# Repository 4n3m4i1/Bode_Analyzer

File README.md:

# Bode Bandits Analysis Tool
The Bode Bandits Analysis Tool provides frequency response characteristics of a multitude of filters.
A Python GUI allows interface with the tool, providing configuration and visual representations of the measured transfer function.  
  
## Hardware
Board and assembly files are provided in the repository, optimized for JLC's PCBA service.  
  
## Methods
The Least Mean Squared (LMS) adaptive filter methodology is implemented in a semi-real time fashion, allowing rapid characterization cycles to be made.  
All algorithms (LMS, FFT, Downsampling) are fully parametric, and largely user selectable on the fly. Automatic self-calibration corrects for  
component tolerance variations, VDDA magnitude, and the frontend anti-aliasing filter transfer function. DC calibration routines are run at  
startup, all transfer function calibration metrics are gathered at startup as well as upon change of any parametric setting.  

## Real Time Adjustment Parameters
- Range of frequency analysis (set ranges)
- Datapoint resolution (2^n)
- Acceptable LMS convergence error tolerances
  
## Required User Software 
- Python 3.9+
- That's it :)
  
## Repo Layout
- App: Contains the PC side of the project. Including the Python source and helper tools.
- HDL: Placeholder for potential HDL in the event a switch to a more PL based approach occurs.
- src: All C source for both the current main build as well as helper C files and feature tests.
- Documentation: All standard documentation as well as theory behind every working component, with test programs and scrips included.

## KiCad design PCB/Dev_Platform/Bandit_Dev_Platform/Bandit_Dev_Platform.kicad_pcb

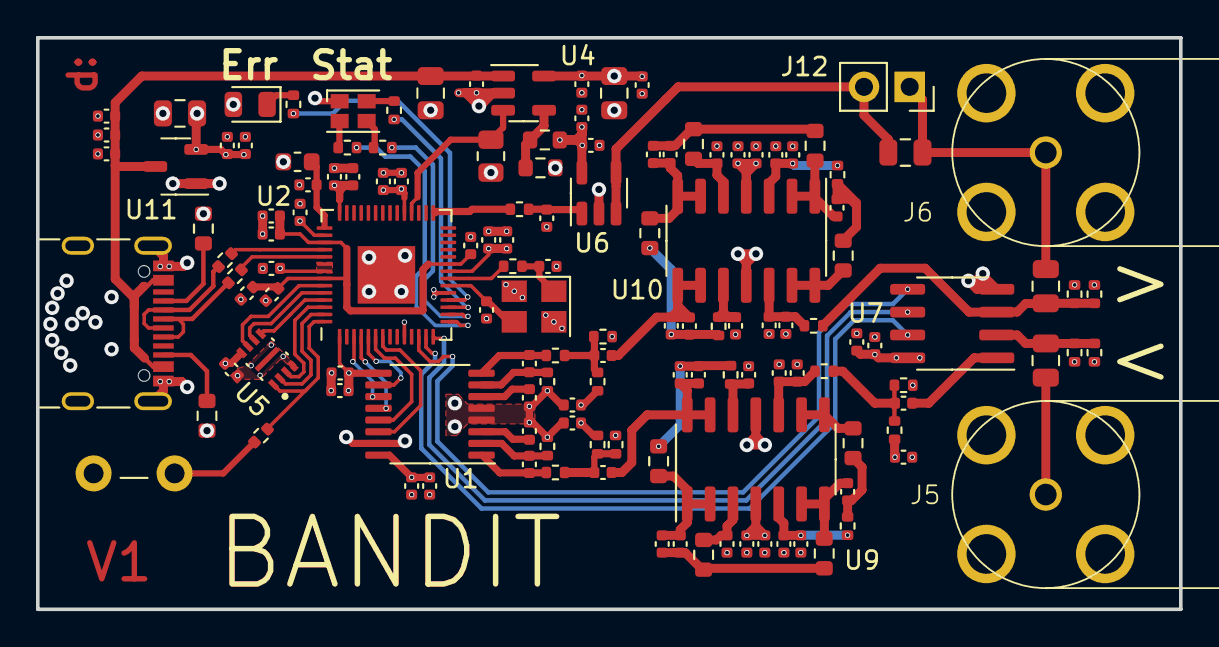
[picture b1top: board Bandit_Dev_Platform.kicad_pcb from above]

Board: 4 copper layers, 63.5 x 31.8 mm, 136 parts (0 on the bottom side), 79 nets.

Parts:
C1, C3, C3#2, C6, C8, C12, C13, C15, C26, C28, C31, C33, C36, C48, C57, C61, C62, C64, C65, C67, C74: 100n; C_0402_1005Metric
C2, C17, C18, C21, C22, C68: 10u; C_0402_1005Metric
C4, C9, C14, C27, C29, C30: 1u; C_0402_1005Metric
C5, C35, C49, C58: 10n; C_0402_1005Metric
C7, C10, C16, C19, C20, C38, C41, C46, C50, C55: 33p C0G; C_0402_1005Metric
C11, C34, C37, C63, C66, C70: 2u2; C_0402_1005Metric
C23, C24: 16n C0G; C_0402_1005Metric
C25, C69, C71, C72, C73, C75: 10u 0805; C_0805_2012Metric
C32: 10n C0G; C_0402_1005Metric
C39, C40, C45, C47, C54, C56: 100p C0G; C_0402_1005Metric
C42, C51: 15p C0G; C_0402_1005Metric
C43, C52: 220p C0G; C_0402_1005Metric
C44, C53, C59, C60: 47p C0G; C_0402_1005Metric
D1: LED; LED_0805_2012Metric
D2: LED_ABGR; LED_Cree-PLCC4_2x2mm_CW
FB1: FerriteBead_Small; L_0603_1608Metric
J5, J6: BNC; DOSIN-801-0050
J12: Conn_01x02_Pin; PinSocket_1x02_P2.54mm_Vertical
P1: USB_C_Plug_USB2.0; USB_C_Receptacle_GCT_USB4105-xx-A_16P_TopMnt_Horizontal
R1, R2, R3, R6: 330R; R_0402_1005Metric
R4, R5: 27R; R_0402_1005Metric
R7: 10k; R_0805_2012Metric
R8: 150k; R_0603_1608Metric
R9: 50k; R_0603_1608Metric
R10, R11: 56k; R_0603_1608Metric
R12, R14: 1k; R_0402_1005Metric
R13, R15, R25, R26: 51k; R_0402_1005Metric
R16, R17, R18, R19, R20, R42: 10k; R_0402_1005Metric
R21, R22, R23, R24: 20R; R_0402_1005Metric
R27: 8.06; R_0402_1005Metric
R28, R32, R35, R39: 15k; R_0402_1005Metric
R29, R36: 8k2; R_0603_1608Metric
R30, R37: 15k; R_0603_1608Metric
R31, R38: 5k6; R_0603_1608Metric
R33, R40: 6k2; R_0603_1608Metric
R34, R41: 12k; R_0402_1005Metric
SW1: SW_SPST; SW_PUSH_6mm
U1: AD7253; TSSOP-16_4.4x5mm_P0.65mm
U2: RP2040; QFN-56-1EP_7x7mm_P0.4mm_EP3.2x3.2mm
U4: NCP164ASNADJT1G; SOT-23-5
U5: W25Q16JVUXIQ_TR; IC_W25Q16JVUXIQ_TR
U6: MCP6486UT-E/OT; SOT-23-5
U7: MCP6S92-E/SN; SOIC-8_3.9x4.9mm_P1.27mm
U9, U10: OPA1664; SOIC-14_3.9x8.7mm_P1.27mm
U11: XC6206PxxxMR; SOT-23-3
Y1: 12.000 MHz, C9002; Crystal_SMD_3225-4Pin_3.2x2.5mm

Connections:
+1V1: C33.1, C34.1, C62.1, C63.1, C64.1, U2.23 (DVDD), U2.45 (VREG_VOUT), U2.50 (DVDD)
+3V3: C1.1, C28.1, C29.1, C35.1, C36.1, C37.1, C61.1, C65.1, C66.1, C67.1, C68.1, C69.1, C70.1, C74.1, D1.2 (A), D2.1 (A), FB1.2, U1.9 (DVDD), U2.1 (IOVDD), U2.10 (IOVDD), U2.22 (IOVDD), U2.33 (IOVDD), U2.42 (IOVDD), U2.44 (VREG_IN), U2.48 (USB_VDD), U2.49 (IOVDD), U5.8 (VCC), U11.2 (VO)
/ADC_CSN: U1.11 (~CS), U2.3 (GPIO1)
/ADC_SCK: U1.12 (SCLK), U2.4 (GPIO2)
/ADC_SDI: U1.10 (SDI), U2.5 (GPIO3)
/ADC_SDO_A: U1.13 (SDO_A), U2.6 (GPIO4)
/ADC_SDO_B: U1.14 (SDO_B), U2.7 (GPIO5)
/CLK_12M: C10.1, U2.20 (XIN), Y1.3
/FLASH_IO0: U2.53 (QSPI_SD0), U5.5 (DI(IO0))
/FLASH_IO1: U2.55 (QSPI_SD1), U5.2 (DO(IO1))
/FLASH_IO2: U2.54 (QSPI_SD2), U5.3 (IO2)
/FLASH_IO3: U2.51 (QSPI_SD3), U5.7 (IO3)
/FLASH_SCK: U2.52 (QSPI_SCLK), U5.6 (CLK)
/LED_B: R1.2, U2.17 (GPIO14)
/LED_G: R2.2, U2.16 (GPIO13)
/LED_R: R3.2, U2.15 (GPIO12)
/PDM_WGN: R27.2, U2.29 (GPIO18)
/PGA_SCK: U2.13 (GPIO10), U7.7 (SCK)
/PGA_SI: U2.14 (GPIO11), U7.6 (SI)
/SE_SIG_A: C18.2, C39.1, C52.1, U10.8, U10.9 (-)
/SE_SIG_B: C17.2, C40.1, C43.1, U9.13 (-), U9.14
/SIG_IN: C2.1, R16.2, R17.1, R34.1
/USB_CC: P1.A5 (CC), R10.1
/USB_D+: R5.2, U2.47 (USB_DP)
/USB_D-: R4.2, U2.46 (USB_DM)
/USB_VCONN: P1.B5 (VCONN), R11.1
/USER_LED: R6.2, U2.18 (GPIO15)
/VDDA_EN: R7.2, U2.32 (GPIO21), U4.3 (EN)
/WGN_OUT: C73.2, J12.2, U6.3 (VIN-), U6.4 (VOUT)
/WGN_OUT_PORT: C72.1, C73.1, J6.1 (In), J12.1
/WGN_PGA_IN: C72.2, R13.2, R15.1, R41.1, U7.3 (CH1)
/XOUT: C7.2, R14.2, Y1.1
/~FLASH_CSN: R12.1, U2.56 (QSPI_SS), U5.1 (~CS)
/~PGA_CS: U2.12 (GPIO9), U7.5 (~CS)
GND: C1.2, C3.2, C3#2.2, C4.2, C5.2, C6.2, C7.1, C8.2, C9.2, C10.2, C11.2, C12.2, C13.2, C14.2, C15.2, C16.1, C19.1, C20.1, C21.2, C22.2, C26.2, C27.2, C28.2, C29.2, C30.2, C31.2, C32.2, C33.2, C34.2, C35.2, C36.2, C37.2, C38.1, C41.1, C42.1, C44.1, C46.1, C48.2, C49.2, C50.1, C51.1, C53.1, C55.1, C57.2, C58.2, C61.2, C62.2, C63.2, C64.2, C65.2, C66.2, C67.2, C68.2, C69.2, C70.2, C71.2, C74.2, C75.2, J5.2 (Ext), J6.2 (Ext), P1.A1 (GND), P1.A12 (GND), P1.B1 (GND), P1.B12 (GND), P1.S1 (SHIELD), R7.1, R9.1, R10.2, R11.2, R15.2, R17.2, R19.2, R21.1, R24.1, R26.2, R42.2, SW1.2 (B), U1.4 (REFGND_A), U1.5 (REFGND_B), U1.15 (GND), U2.19 (TESTEN), U2.57 (GND), U4.2 (GND), U5.4 (GND), U6.2 (VSS), U7.4 (VSS), U9.11 (V-), U10.11 (V-), U11.1 (GND), Y1.2, Y1.4
unnamed: C17.1, R18.2, R19.1, R23.1
unnamed: C18.1, R20.2, R22.1, R42.1
unnamed: C39.2, C52.2, R35.1, R36.2
unnamed: C40.2, C43.2, R28.1, R29.2
unnamed: C45.2, C60.2, R30.1, R31.2
unnamed: C47.2, R32.1, R33.2
unnamed: C54.2, C59.2, R37.1, R38.2
unnamed: C56.2, R39.1, R40.2
unnamed: D1.1 (K), R6.1
unnamed: D2.2 (BK), R1.1
unnamed: D2.3 (GK), R2.1
unnamed: D2.4 (RK), R3.1
unnamed: C25.1, J5.1 (In)
unnamed: P1.A6 (D+), R5.1
unnamed: P1.A7 (D-), R4.1
unnamed: R12.2, SW1.1 (A)
unnamed: C24.2, R24.2, U1.2 (AINM_A)
unnamed: C23.2, R21.2, U1.7 (AINM_B)
unnamed: C24.1, R23.2, U1.1 (AINP_A)
unnamed: C23.1, R22.2, U1.8 (AINP_B)
unnamed: C22.1, U1.3 (REFIO_A)
unnamed: C21.1, U1.6 (REFIO_B)
unnamed: C11.1, FB1.1, U2.43 (ADC_AVDD)
unnamed: R14.1, U2.21 (XOUT)
unnamed: R8.1, R9.2, U4.4 (PG/ADJ)
unnamed: C32.1, R27.1, U6.1 (VIN+)
unnamed: C25.2, R25.2, R26.1, U7.2 (CH0)
unnamed: C2.2, U7.1 (VOUT)
unnamed: C44.2, R30.2, U9.3 (+)
unnamed: C45.1, C60.1, R29.1, U9.1, U9.2 (-)
unnamed: C16.2, C46.2, R32.2, U9.5 (+)
unnamed: C47.1, R31.1, U9.6 (-), U9.7
unnamed: C19.2, C50.2, R34.2, U9.10 (+)
unnamed: R33.1, U9.8, U9.9 (-)
unnamed: C42.2, R28.2, U9.12 (+)
unnamed: C38.2, C55.2, R39.2, U10.3 (+)
unnamed: C56.1, R38.1, U10.1, U10.2 (-)
unnamed: C53.2, R37.2, U10.5 (+)
unnamed: C54.1, C59.1, R36.1, U10.6 (-), U10.7
unnamed: C51.2, R35.2, U10.10 (+)
unnamed: C20.2, C41.2, R41.2, U10.12 (+)
unnamed: R40.1, U10.13 (-), U10.14
VBUS: C3.1, C4.1, C5.1, C6.1, C75.1, P1.A4 (VBUS), P1.A9 (VBUS), P1.B4 (VBUS), P1.B9 (VBUS), U4.1 (VIN), U11.3 (VI)
VDDA: C3#2.1, C8.1, C9.1, C12.1, C13.1, C14.1, C15.1, C26.1, C27.1, C30.1, C31.1, C48.1, C49.1, C57.1, C58.1, C71.1, R8.2, R13.1, R16.1, R18.1, R20.1, R25.1, U1.16 (AVDD), U4.5 (VOUT), U6.5 (VDD), U7.8 (VDD), U9.4 (V+), U10.4 (V+)

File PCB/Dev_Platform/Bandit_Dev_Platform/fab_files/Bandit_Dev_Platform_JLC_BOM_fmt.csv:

Designator,Qty,Value,Footprint,LCSC Part Number,
"C1, C3, C6, C8, C12, C13, C15, C26, C28, C31, C33, C36, C48, C57, C61, C62, C64, C65, C67, C74",20,100n,Capacitor_SMD:C_0402_1005Metric,C307331,
"C2, C17, C18, C21, C22, C68",6,10u,Capacitor_SMD:C_0402_1005Metric,C15525,
"C4, C9, C14, C27, C29, C30",6,1u,Capacitor_SMD:C_0402_1005Metric,C52923,
"C5, C35, C49, C58",4,10n,Capacitor_SMD:C_0402_1005Metric,C15195,
"C7, C10, C19, C20, C41, C50",6,33p C0G,Capacitor_SMD:C_0402_1005Metric,C1562,
"C11, C34, C37, C63, C66",6,2u2,Capacitor_SMD:C_0402_1005Metric,C12530,
"C16, C38, C46, C55",4,33p,C0G,Capacitor_SMD:C_0402_1005Metric,C1562
"C23, C24",2,16n C0G,Capacitor_SMD:C_0402_1005Metric,C1549,
"C25, C69, C70, C71, C72, C73",5,10u 0805,Capacitor_SMD:C_0805_2012Metric,C440198,
C32,1,10n C0G,Capacitor_SMD:C_0402_1005Metric,C15195,
"C39, C40, C45, C47, C54, C56",6,100p,C0G,Capacitor_SMD:C_0402_1005Metric,C1546
"C42, C51",2,15p   C0G,Capacitor_SMD:C_0402_1005Metric,C1548,
C43,1,220p,C0G,Capacitor_SMD:C_0402_1005Metric,C1530
"C44, C53, C59, C60",4,47p,C0G,Capacitor_SMD:C_0402_1005Metric,C1567
C52,1,220p C0G,Capacitor_SMD:C_0402_1005Metric,C1530,
D1,1,LED,LED_SMD:LED_0805_2012Metric,C2297,
D2,1,LED_ABGR,LED_SMD:LED_Cree-PLCC4_2x2mm_CW,C2874119,
FB1,1,FerriteBead_Small,Inductor_SMD:L_0603_1608Metric,C1002,
"J5, J6",2,BNC,BANDIT_PCB_Lib:DOSIN-801-0050,C521210,
P1,1,USB_C_Plug_USB2.0,Connector_USB:USB_C_Receptacle_GCT_USB4105-xx-A_16P_TopMnt_Horizontal,C963413,
"R1, R2, R3, R6",4,330R,Resistor_SMD:R_0402_1005Metric,C25104,
"R4, R5",2,27R,Resistor_SMD:R_0402_1005Metric,C25092,
R7,1,100k,Resistor_SMD:R_0805_2012Metric,C149504,
R8,1,150k,Resistor_SMD:R_0603_1608Metric,C22807,
R9,1,50k,Resistor_SMD:R_0603_1608Metric,C23184,
"R10, R11",2,56k,Resistor_SMD:R_0603_1608Metric,C23206,
"R12, R14",2,1k,Resistor_SMD:R_0402_1005Metric,C11702,
"R13, R15, R25, R26",4,51k,Resistor_SMD:R_0402_1005Metric,C25794,
"R16, R17, R18, R19, R20, R42",6,10k,Resistor_SMD:R_0402_1005Metric,C25744,
"R21, R22, R23, R24",4,20R,Resistor_SMD:R_0402_1005Metric,C25092,
R27,1,8.06,Resistor_SMD:R_0402_1005Metric,C25077,
"R28, R32, R35, R39",4,15k,Resistor_SMD:R_0402_1005Metric,C25867,
"R29, R36",2,8k2,Resistor_SMD:R_0603_1608Metric,C25981,
"R30, R37",2,15k,Resistor_SMD:R_0603_1608Metric,C22809,
"R31, R38",2,5k6,Resistor_SMD:R_0603_1608Metric,C23189,
"R33, R40",2,6k2,Resistor_SMD:R_0603_1608Metric,C4260,
"R34, R41",2,12k,Resistor_SMD:R_0402_1005Metric,C25752,
U2,1,RP2040,Package_DFN_QFN:QFN-56-1EP_7x7mm_P0.4mm_EP3.2x3.2mm,C2040,
U5,1,W25Q16JVUXIQ_TR,ICDB_Curly:IC_W25Q16JVUXIQ_TR,C2843335,
U11,1,XC6206PxxxMR,Package_TO_SOT_SMD:SOT-23-3,C5446,
Y1,1,"	12.000 MHz, C9002 ",Crystal:Crystal_SMD_3225-4Pin_3.2x2.5mm,C9002,

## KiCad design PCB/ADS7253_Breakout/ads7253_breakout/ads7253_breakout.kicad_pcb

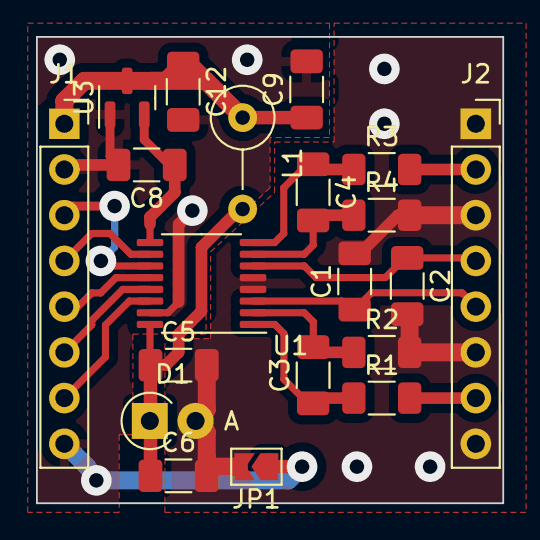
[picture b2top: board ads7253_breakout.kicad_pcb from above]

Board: 2 copper layers, 25.9 x 25.9 mm, 20 parts (0 on the bottom side), 18 nets.

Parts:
C1, C2: 10u; C_1206_3216Metric_Pad1.33x1.80mm_HandSolder
C3, C4: 16p; C_1206_3216Metric_Pad1.33x1.80mm_HandSolder
C5, C9, C12: 1u; C_1206_3216Metric_Pad1.33x1.80mm_HandSolder
C6, C8: 100n; C_1206_3216Metric_Pad1.33x1.80mm_HandSolder
D1: D_Zener; D_T-1_P2.54mm_Vertical_AnodeUp
J1, J2: Conn_01x08_Pin; PinSocket_1x08_P2.54mm_Vertical
JP1: Jumper_2_Bridged; SolderJumper-2_P1.3mm_Open_TrianglePad1.0x1.5mm
L1: L; L_Axial_L7.0mm_D3.3mm_P5.08mm_Vertical_Fastron_MICC
R1, R2, R3, R4: 20R; R_1206_3216Metric_Pad1.30x1.75mm_HandSolder
U1: AD7253; TSSOP-16_4.4x5mm_P0.65mm
U3: MCP1700x-330xxTT; SOT-23

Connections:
+3V3: C8.1, U1.9 (DVDD), U3.2 (VO)
+5C: C9.1, C12.1, J1.1, L1.1, U3.3 (VI)
/AINP_A_1: J2.7, R1.2
/AINP_B_8: J2.2, R3.2
/REFDAC_A: C1.1, J2.5, U1.3 (REFIO_A)
/REFDAC_B: C2.1, J2.4, U1.6 (REFIO_B)
/SPI_CSN: J1.3, U1.11 (~CS)
/SPI_SCLK: J1.5, U1.12 (SCLK)
/SPI_SDI: J1.4, U1.10 (SDI)
/SPI_SDOA: J1.6, U1.13 (SDO_A)
/SPI_SDOB: J1.7, U1.14 (SDO_B)
GND: C8.2, C9.2, C12.2, J1.2, J1.8, JP1.1 (A), U1.15 (GND), U3.1 (GND)
GNDA: C1.2, C2.2, C5.2, C6.2, D1.2 (A), J2.1, J2.3, J2.6, J2.8, JP1.2 (B), R2.2, R4.2, U1.4 (REFGND_A), U1.5 (REFGND_B)
unnamed: C3.2, R2.1, U1.2 (AINM_A)
unnamed: C4.2, R4.1, U1.7 (AINM_B)
unnamed: C3.1, R1.1, U1.1 (AINP_A)
unnamed: C4.1, R3.1, U1.8 (AINP_B)
VDDA: C5.1, C6.1, D1.1 (K), L1.2, U1.16 (AVDD)

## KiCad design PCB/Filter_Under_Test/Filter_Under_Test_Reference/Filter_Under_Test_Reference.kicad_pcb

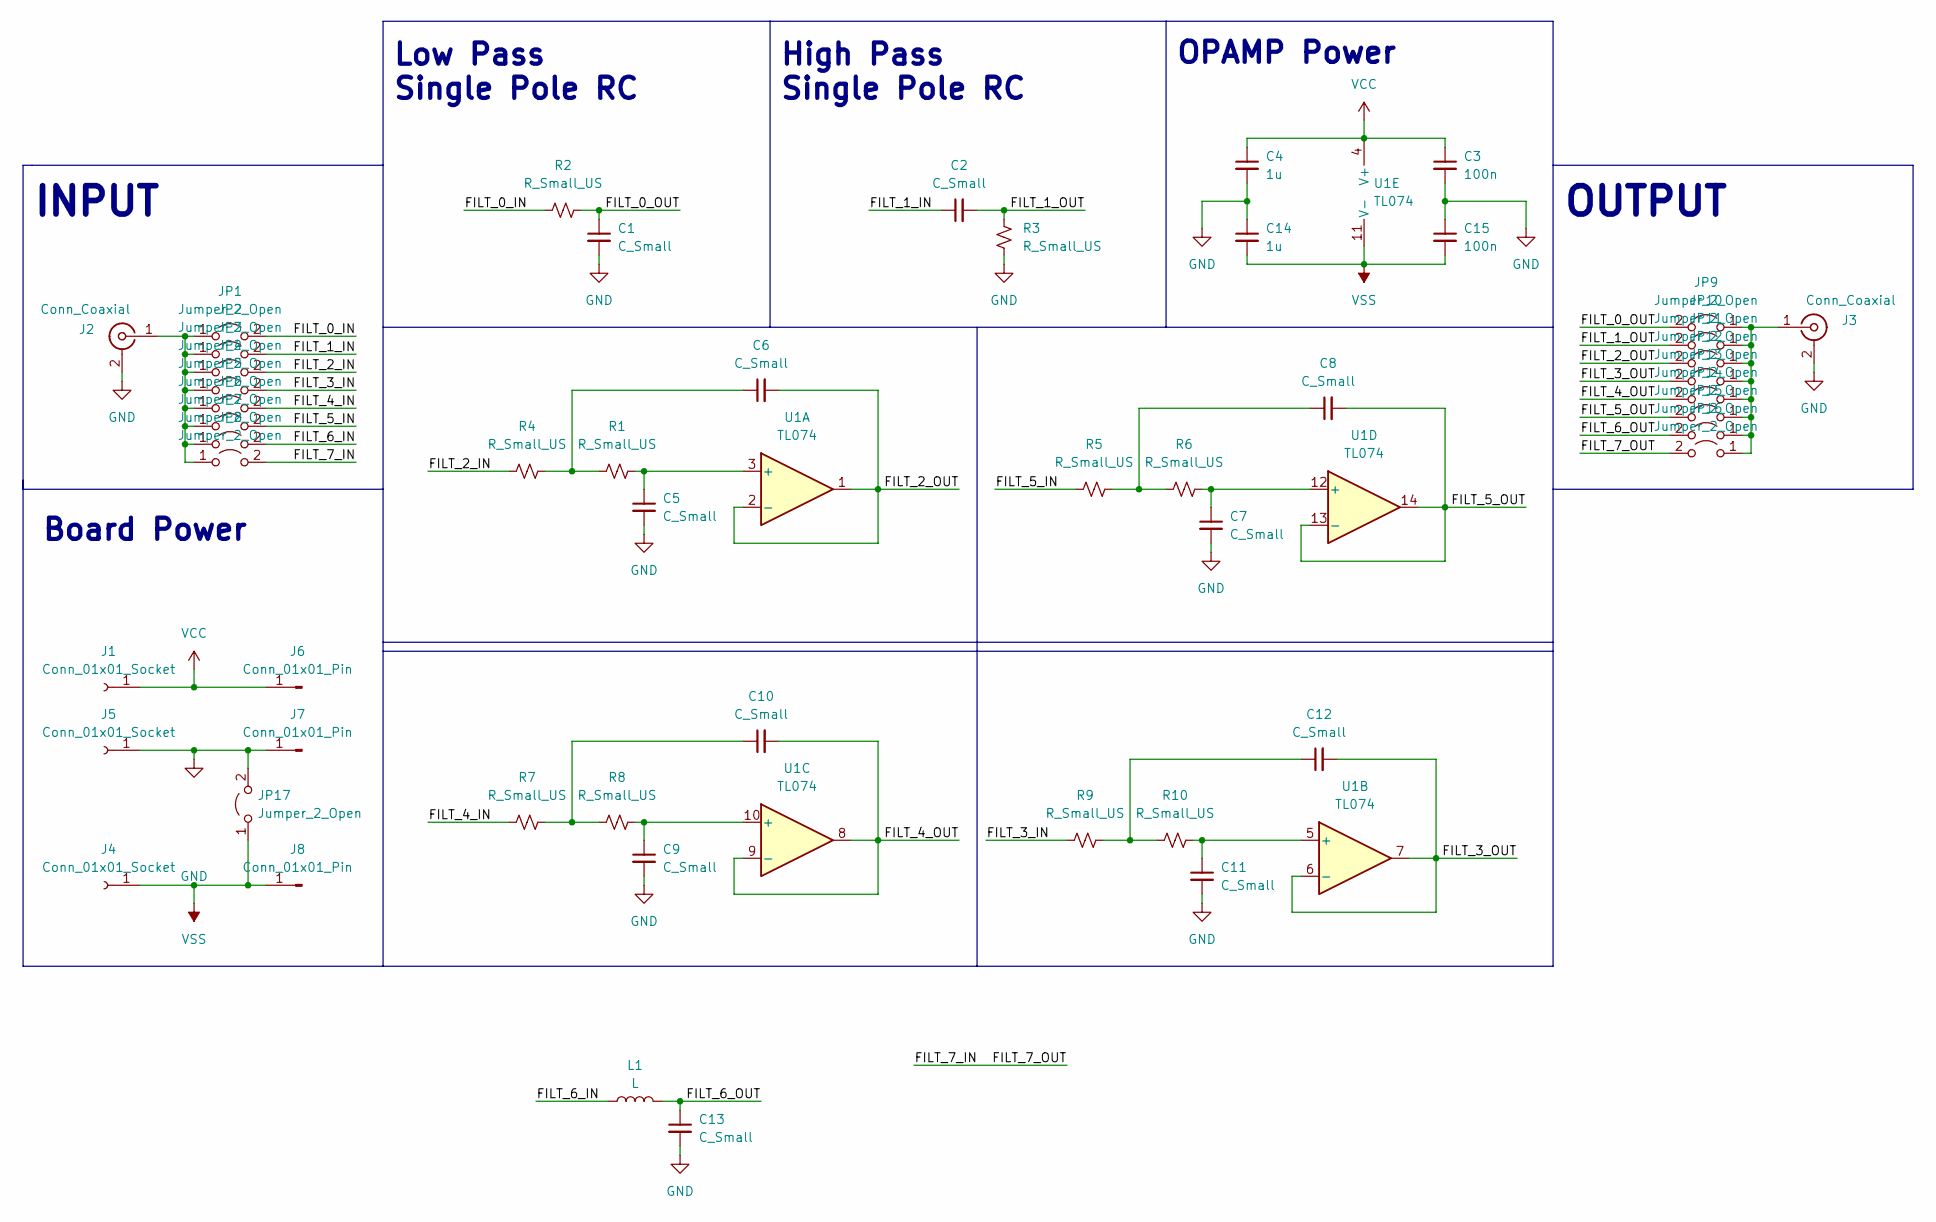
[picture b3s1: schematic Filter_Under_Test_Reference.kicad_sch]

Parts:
C1, C2, C5, C6, C7, C8, C9, C10, C11, C12, C13: C_Small; C_1206_3216Metric_Pad1.33x1.80mm_HandSolder
C3, C15: 100n; C_0805_2012Metric_Pad1.18x1.45mm_HandSolder
C4, C14: 1u; C_0805_2012Metric_Pad1.18x1.45mm_HandSolder
J1, J4, J5: Conn_01x01_Socket; Keystone 575 Banana
J2, J3: Conn_Coaxial; BNC_THT
J6, J7, J8: Conn_01x01_Pin; PinSocket_1x01_P2.54mm_Vertical
JP1, JP2, JP3, JP4, JP5, JP6, JP7, JP8, JP9, JP10, JP11, JP12, JP13, JP14, JP15, JP16, JP17: Jumper_2_Open; PinSocket_1x02_P2.54mm_Vertical
L1: L; L_Axial_L5.3mm_D2.2mm_P7.62mm_Horizontal_Vishay_IM-1
R1, R2, R3, R4, R5, R6, R7, R8, R9, R10: R_Small_US; R_1206_3216Metric_Pad1.30x1.75mm_HandSolder
U1: TL074; SOT23 Thin 14

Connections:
/FILT_0_IN: JP1.2 (B), R2.1
/FILT_0_OUT: C1.1, JP9.2 (B), R2.2
/FILT_1_IN: C2.1, JP2.2 (B)
/FILT_1_OUT: C2.2, JP10.2 (B), R3.1
/FILT_2_IN: JP3.2 (B), R4.1
/FILT_2_OUT: C6.2, JP11.2 (B), U1.1, U1.2 (-)
/FILT_3_IN: JP4.2 (B), R9.1
/FILT_3_OUT: C12.2, JP12.2 (B), U1.6 (-), U1.7
/FILT_4_IN: JP5.2 (B), R7.1
/FILT_4_OUT: C10.2, JP13.2 (B), U1.8, U1.9 (-)
/FILT_5_IN: JP6.2 (B), R5.1
/FILT_5_OUT: C8.2, JP14.2 (B), U1.13 (-), U1.14
/FILT_6_IN: JP7.2 (B), L1.1
/FILT_6_OUT: C13.1, JP15.2 (B), L1.2
/FILT_7_IN: JP8.2 (B), JP16.2 (B)
GND: C1.2, C3.2, C4.2, C5.2, C7.2, C9.2, C11.2, C13.2, C14.1, C15.1, J2.2 (Ext), J3.2 (Ext), J5.1, J7.1, JP17.2 (B), R3.2
unnamed: C6.1, R1.1, R4.2
unnamed: C8.1, R5.2, R6.1
unnamed: C10.1, R7.2, R8.1
unnamed: C12.1, R9.2, R10.1
unnamed: J2.1 (In), JP1.1 (A), JP2.1 (A), JP3.1 (A), JP4.1 (A), JP5.1 (A), JP6.1 (A), JP7.1 (A), JP8.1 (A)
unnamed: J3.1 (In), JP9.1 (A), JP10.1 (A), JP11.1 (A), JP12.1 (A), JP13.1 (A), JP14.1 (A), JP15.1 (A), JP16.1 (A)
unnamed: C5.1, R1.2, U1.3 (+)
unnamed: C11.1, R10.2, U1.5 (+)
unnamed: C9.1, R8.2, U1.10 (+)
unnamed: C7.1, R6.2, U1.12 (+)
VCC: C3.1, C4.1, J1.1, J6.1, U1.4 (V+)
VSS: C14.2, C15.2, J4.1, J8.1, JP17.1 (A), U1.11 (V-)

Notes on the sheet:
High Pass Single Pole RC
Low Pass Single Pole RC
OPAMP Power
OUTPUT
Board Power
INPUT

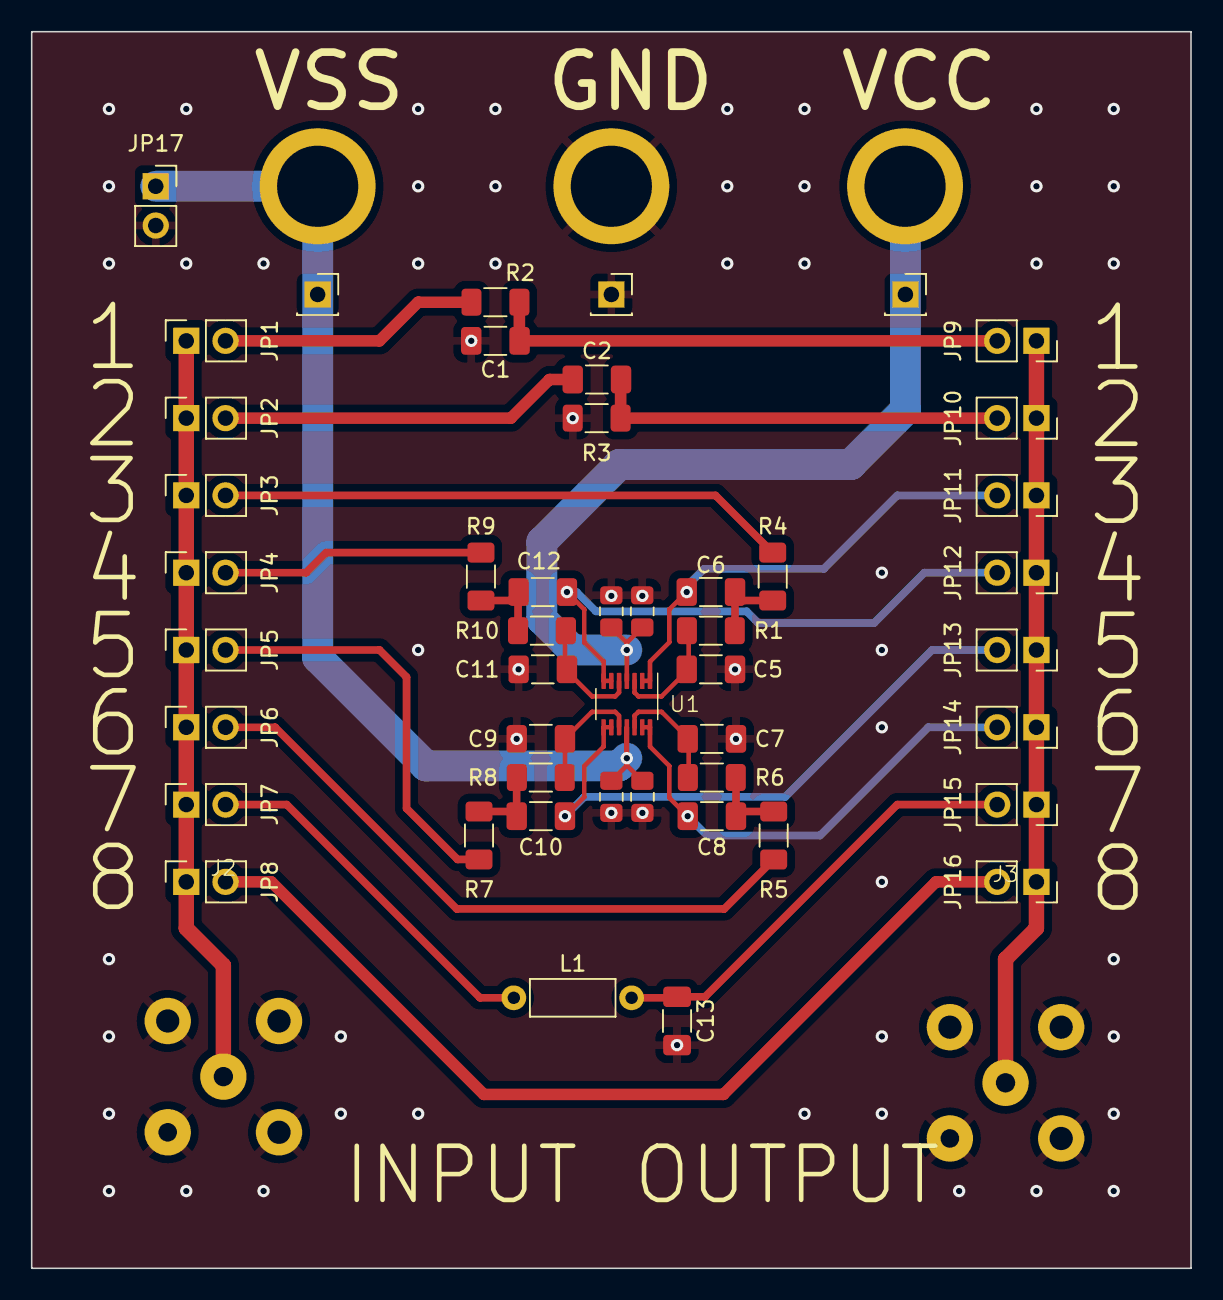
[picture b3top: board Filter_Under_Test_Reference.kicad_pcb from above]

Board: 2 copper layers, 75.0 x 80.0 mm, 52 parts (0 on the bottom side), 28 nets.

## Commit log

2023-09-18 Fixed math in markdown
2023-09-18 Fixed some file structure
2023-09-18 Added more DSP math
2023-09-18 Added Octave example of lock in theory
2023-09-19 More math...
2023-09-20 Moved things around
2023-09-21 Added RP2040 testbench/structure
2023-09-28 Added some tooling
2023-10-04 Big modification
2023-10-05 Cool adaptive filter simulation done :)
2023-10-05 Fixed out of range conditions
2023-10-06 Fixed readme, made DSP Adaptive test more safe for failure conditions
2023-10-08 Added cool animation creation method for visualizing learning algorithms
2023-10-08 Removed KST with local paths
2023-10-08 Added frame stride to fix videos to ~1000 frames
2023-10-09 Fixed weird gif colors w/ dynamic ffmpeg palettes
2023-10-09 Image test
2023-10-09 Is it pretty yet?
2023-10-09 Is it pretty yet???
2023-10-09 Is it pretty yet????
2023-10-09 okay... I think this worked... I'm bad at typing
2023-10-09 Josh was here
2023-10-09 Working back from really bad break in C source
2023-10-10 Added new riemann sum error output term
2023-10-12 Added dev platform schematic, project kicad library, got AWGN down
2023-10-12 Added baseline for testing USB CDC transfers w/ TinyUSB
2023-10-12 Moved Datastreaming test to /src/tests
2023-10-12 Fixed README
2023-10-12 Minor fixes
2023-10-16 Super scuffed but CTRL and DATA channel dual ACM kinda parametric and working
2023-10-16 Absolutely garbage code quality, will clean later. 780kBps measured!
2023-10-17 Small tool for double -> Q15 conversion, need to finish file handling part
2023-10-18 initial changes for serial read
2023-10-19 Added structure for prototype activity
2023-10-24 PIO DMA White noise generator sketch
2023-10-25 Okay now it worky
2023-10-25 PIO properly initiates pin, main core setting not needed anymore
2023-10-25 forgot what I changed
2023-10-26 Added instructions for building RP2040 code
2023-10-26 initial commit for tinyusb test
2023-10-26 created send packet functions for each datatype
2023-10-26 fix state init
2023-10-26 Added FFT example modified from VHA, more modifications coming
2023-10-26 Swap to struct and dynamic structure for variable length
2023-10-26 Allowed pico_sdk_import.cmake thru gitignore
2023-10-27 fixes
2023-11-01 Added matlab stuff
2023-11-03 adaptive-filter-init
2023-11-03 fix plots
2023-11-03 Some Shit
2023-11-04 integrated control channel into state machine which now allows for the data to be initialized and sent
2023-11-09 Added timing Analytics
2023-11-11 Downsampling test, not done..
2023-11-11 Initial setup for Development Platform
2023-11-11 Oopsie lock file include
2023-11-16 Update dev sch
2023-11-16 Added parts list
2023-11-20 Added MCP6S92-E/SN
2023-11-21 Filter added to PCB
2023-11-21 added initial serial input testing
2023-11-21 beep
2023-11-21 Wooooo
2023-11-21 Added Filter Round 2
2023-11-21 protocol for device init
2023-11-21 started dev platform PCB
2023-11-21 update pcb, filter kinda done
2023-11-21 Josh said the tracks are great
2023-11-27 Fixing dev pcb
2023-11-27 Initial USB protocol draft
2023-11-28 PCB Fun
2023-11-30 PCB Update
2023-12-05 PCB Updates
2024-01-29 Started 0402 transition, PN conversions for fabrication
2024-01-30 Pcb kinda worked on
2024-01-31 Added circular buffer test, library otw
2024-01-31 Circular buffers added to RP2040 evaluation stack
2024-02-01 Fixed makefile for eval, linking is pretty good now
2024-02-01 Restructured FFT trig tables, ensured a single table can cover all expected FFT sizes
2024-02-01 Working on linker script again, if not it's super sketchy diy allocation time
2024-02-01 Builds with custom linker, cmake and include issues solved
2024-02-01 I think custom linking works correctly, need to verify 100% but build and objdump look okay
2024-02-01 More setup on general structure, probably need to block diagram this out soon...
2024-02-01 Fast FIR working w/ circular buffers library for any 2^n
2024-02-02 Okay it works now :)
2024-02-02 Polyphase decimation soon
2024-02-05 Fixed filter to be cheap
2024-02-05 PCB stuff
2024-02-05 Fixed BNC issue, changed more parts to be free.99
2024-02-05 Almost done w pcb
2024-02-06 Done?
2024-02-06 More done
2024-02-06 Schematic cleanup
2024-02-06 Started fab files, idiot checking pcb
2024-02-07 Added filter test board
2024-02-10 Dev platform and Filter Test pcb polished, ordered
2024-02-10 Need to update fab, but fixed C70 duplicate issue from version mismatch
2024-02-12 ack data-streaming test
2024-02-12 comm port ack bit initial
2024-02-12 initial ack com frontend
2024-02-15 Really tired so ADS library is super unfinished, don't use or reference... yet
2024-02-22 test plot - dummy data
2024-02-22 initialize gui
2024-02-24 Added Bandit_Pins header, RUN pin wasn't tied high.. hopefully wont be an issue lol
2024-02-24 Blink Sketch built off of template
2024-02-26 ADC Workin
2024-02-26 PGA Working, signal present to ADC. ADC Data not great
2024-02-27 initial multiprocessing TODO: fix graph updating and graph object communication between processes
2024-02-29 made graph faster w multiprocessing instead of threading
2024-02-29 added start and stop capabilities
2024-03-05 fix data transfer delay + initial GUI improvements
2024-03-05 data transfer fixes
2024-03-06 Added parametric taps setting
2024-03-07 added port selection capabilities for mac
2024-03-07 changed README
2024-03-07 port selection exception handling
2024-03-07 code cleanup
2024-03-07 more exception handling
2024-03-07 sorry one more exception handling
2024-03-07 when main thread ends, all other threads exit
2024-03-07 Added better configuration input
2024-03-08 Issue narrowed down to pin overwrite with PIO, works fine in vacuum... Will fix tomorrow
2024-03-08 Raw PIO SPI added
2024-03-08 Added frequency range setting
2024-03-08 added frequency ranges setting
2024-03-15 Beep boop closer
2024-03-15 MOSI not working, the rest is. REference PIO_ADS7253 for working MISO, will crack tmrw or something
2024-03-18 Added about us page
2024-03-21 Mostly working, some weird desync but can be dealt with :)
2024-03-21 Restructuring, updated Bandit_Template
2024-03-26 Added linux
2024-03-28 add more fixes
2024-03-28 Wee woo template usb
2024-03-28 commiting
2024-03-28 added pyc to gitignore
2024-03-28 Changed styling to pink
2024-03-30 added initial USB_handling protocol and initial core 0 state machine
2024-03-30 FIxed Bandit Template
2024-03-30 Compiled Bandit_Template_USB, no functional verification, finifhing ADC library
2024-03-31 Cleaned up library, it's a bit wack but it do be workin
2024-03-31 PIO ADC fully integrated with Bandit Template :)
2024-03-31 Added sampling cycle specific functionality for dual SDOs
2024-03-31 Synchronized sampling specific routines between feature tests and Bandit Template
2024-03-31 Added 500ksps sampling to main state machine :)
2024-03-31 Got rid of bad template
2024-03-31 Cleanup
2024-03-31 Backported USB into Template
2024-03-31 Cleanup, will branch new USB dev in a bit
2024-04-01 Most of inter-core sync and data transfer done, development can now be decoupled between cores/teams :)
2024-04-01 forgot to add files :p
2024-04-01 Uhhh calibration routine probably mostly there
2024-04-01 Settings application logic and semaphores implemented
2024-04-01 Better handling of DC calibration vs. runtime h(t) offset
2024-04-01 Cleanup of utilities
2024-04-01 Added AHB Mux priority sets for 0 wait state real time operation
2024-04-01 Cleanup of memory accesses, removed ping pong h_hat transfer
2024-04-01 Added LMS sample counter, Fast AHB collision counter, cleaned up state logic
2024-04-01 Fixed missing PGA settling time, parameterized PGA settling time
2024-04-03 Added DAC adjustment test, Bandit passed. Moved files
2024-04-03 Added and tested ADS7253 REFDAC auto calibration routine
2024-04-03 Added Debug struct so we can peer inside the Bandit during runtime
2024-04-03 Added Bandit Debug tracking for Core 1
2024-04-03 WGN on/off added to state machine. Do NOT use debug mode, state will lock core 1
2024-04-04 Added default LMS Struct w/ settings, this cascades into allowing a default set state that will also change FFT settings OTF if a user resets to default state
2024-04-04 Added bank downsampling in LMS looping
2024-04-04 Fixed LMS loop bounds when in downsampling mode
2024-04-04 instructions on tap length update
2024-04-04 GUI glow up
2024-04-04 Testing build million NOP sampling is super accurate, so it stays... lol
2024-04-04 Cleanup, Fs validated
2024-04-04 organized gui code, wrote code for a dynamic table
2024-04-04 Added FIR Filter
2024-04-04 added table changes
2024-04-05 Added Downsampling woo
2024-04-05 added setting config and fixed isr
2024-04-05 removed all wait state from Core 1 settings bitfield access
2024-04-05 Weird downsampling broken
2024-04-05 Compiles :)
2024-04-05 Love that
2024-04-05 first go
2024-04-05 first
2024-04-06 added dynamic table of selected configs on main page
2024-04-06 GUI fixing
2024-04-07 Made it compile.......
2024-04-08 BROKEN
2024-04-08 fix comm
2024-04-08 crossplat
2024-04-08 crossplat - linux
2024-04-08 crossplat - linux bleh
2024-04-08 it works on linux now
2024-04-08 asdna
2024-04-08 settings worky
2024-04-08 Debug gettin implemented yee haw
2024-04-08 Bandit is stuck on ADC setup again... shouldn't be
2024-04-08 On/Off WGN verified, USB settings can be reapplied on the fly
2024-04-09 Okay, it works with fixed lengths and is awful. Stall on LMS params passed thru USB, not sure where the disconnect is
2024-04-09 added WGN switch
2024-04-09 Preparations for intercore FIFO debug messaging
2024-04-09 Fixed intercore (spec: messaging) library organization
2024-04-09 Error somewhere in core 0 state machine
2024-04-10 fixed some GUI transfer and grpahing bugs
2024-04-10 quick fixes
2024-04-10 Printing sorta works, FFT results always 0
2024-04-12 fixed graph scaling 1
2024-04-12 It's workingggggg (mostly)
2024-04-12 GUI hehe
2024-04-12 added more settings and bf
2024-04-13 Found error in FFT :)
2024-04-13 FFT Fixed, table shift indexing was being done slightly wrong :)
2024-04-13 Fixed flags, reset LEDs to operational Core 1 tracking
2024-04-15 Working branch w/ stripped communications for DSP debugging
2024-04-15 Working FFT finally, dumb memory map issue
2024-04-16 Testing program is helpful
2024-04-16 add new settings config
2024-04-16 Convolved
2024-04-17 in process
2024-04-17 fixed gui for windowsssssss
2024-04-17 added 2nd config table
2024-04-18 GUI glow up V2
2024-04-25 lots
2024-04-25 weeee
2024-04-25 blaj
2024-04-25 big testing moment
2024-04-25 oops
2024-04-25 added pycache to gitignore
2024-04-25 same
2024-04-25 deletion
2024-04-26 improving UI
2024-04-26 python changes are like not in here :(
2024-04-26 updating about us
2024-04-26 updating branch
2024-04-27 A more appealing GUI
2024-04-29 back to blaj
2024-04-29 new start and stop
2024-04-29 Theory
2024-04-30 more force stuff
2024-04-30 Wee woooooo
2024-04-30 added single shot btn
2024-04-30 back to threading
2024-05-01 INIT
2024-05-01 wee woooooo she be workin
2024-05-01 settings print back correctly now
2024-05-01 DELAY FIX
2024-05-01 Not working w old code... hmmm
2024-05-01 THIS IS THE BUILD FOR THE DAY DO NOT CHANGE PLS REVERT IF BROKE
2024-05-01 uyup
2024-05-01 GUI Prettier
2024-05-01 yyeyeyey
2024-05-01 Final build for design day functional branch
2024-05-04 Bode Bandit Moment
2024-05-06 Tenatively working, freq domain self calibration no worky
2024-05-06 Removed autocal H(s) until it works better
2024-05-06 init_windows
2024-05-06 Trying to log graph, no line output
2024-05-06 TImeout for USB disconnects at bad times, fixed persistent compile errors
2024-05-06 getting graph scaling
2024-05-06 yeyeye
2024-05-06 Stash
